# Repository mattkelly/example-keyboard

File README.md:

# example-keyboard

An example 4-key keyboard based on https://github.com/ruiqimao/keyboard-pcb-guide, with the following changes:

- Kailh Choc PG1350 switches
- Updated for KiCad 5
- 4-pin crystal in schematic to match footprint

## Firmware

Example QMK-based firmware is available on the [`example-keyboard` branch of my QMK fork](https://github.com/mattkelly/qmk_firmware/tree/example-keyboard/keyboards/example_keyboard).

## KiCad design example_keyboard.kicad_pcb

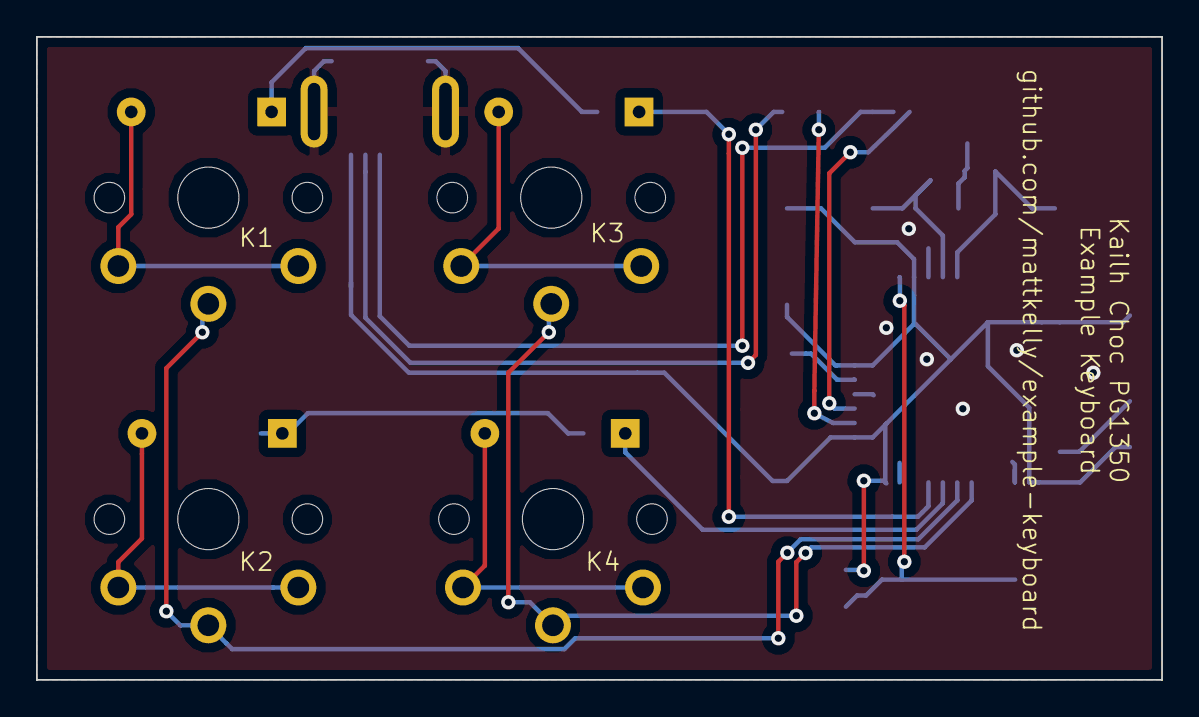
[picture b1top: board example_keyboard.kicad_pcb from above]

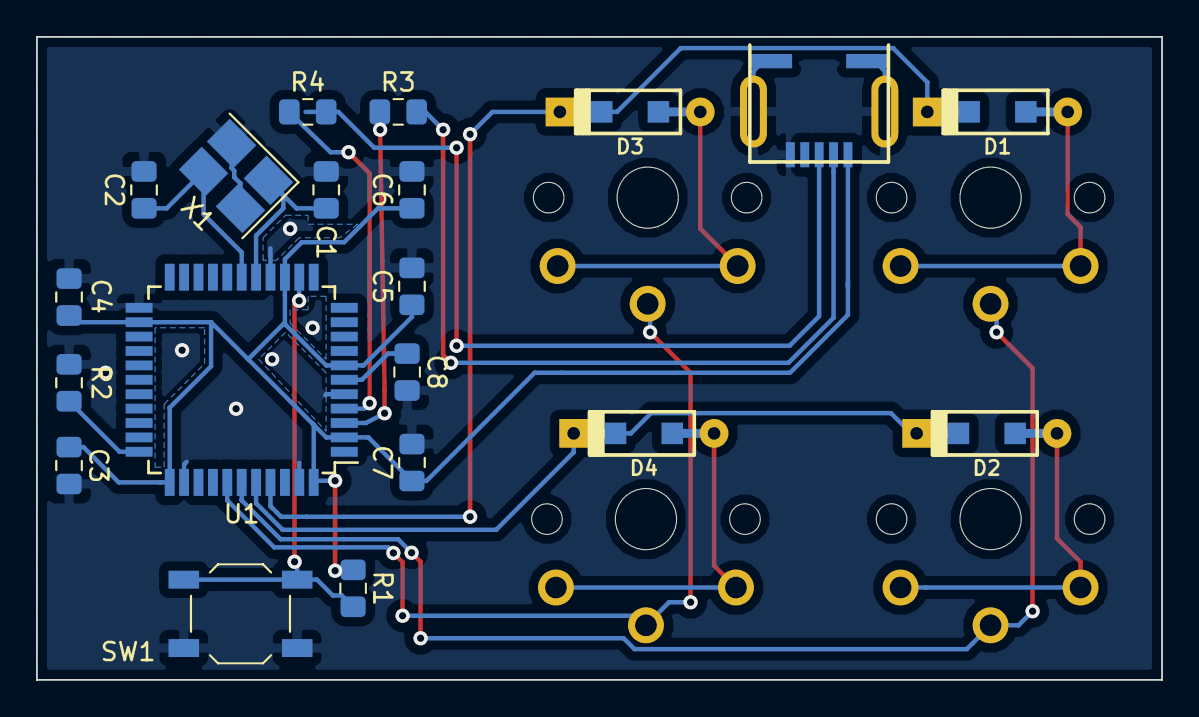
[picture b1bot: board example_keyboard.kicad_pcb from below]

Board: 2 copper layers, 62.5 x 35.7 mm, 24 parts (20 on the bottom side), 19 nets.

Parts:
C1, C2: 22p; C_0805_2012Metric_Pad1.15x1.40mm_HandSolder
C3, C4, C5, C6: 0.1u; C_0805_2012Metric_Pad1.15x1.40mm_HandSolder
C7: 4.7u; C_0805_2012Metric_Pad1.15x1.40mm_HandSolder
C8: 1u; C_0805_2012Metric_Pad1.15x1.40mm_HandSolder
D1, D2, D3, D4: D; D_SOD123_axial
J1: USB_mini_micro_B; USB_miniB_hirose_5S8
K1, K2, K3, K4: KEYSW; Kailh-PG1350-1u-reversible_NO_LED
R1, R2: 10k; R_0805_2012Metric_Pad1.15x1.40mm_HandSolder
R3, R4: 27; R_0805_2012Metric_Pad1.15x1.40mm_HandSolder
SW1: SW_PUSH; SW_SPST_TL3342
U1: ATMEGA32U4; TQFP-44_10x10mm_P0.8mm
X1: Crystal_GND24; Crystal_SMD_SeikoEpson_FA238-4Pin_3.2x2.5mm_HandSoldering

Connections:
/col0: K1.1, K2.1, U1.39
/col1: K3.1, K4.1, U1.38
/row0: D1.1, D3.1, U1.41
/row1: D2.1, D4.1, U1.40
GND: C1.2, C2.2, C3.2, C4.2, C5.2, C6.2, C7.2, C8.2, J1.5, J1.6, R2.2, SW1.1, U1.5, U1.15, U1.23, U1.35, U1.43, X1.2, X1.4
unnamed: C1.1, U1.16, X1.1
unnamed: C2.1, U1.17, X1.3
unnamed: C8.1, U1.6
unnamed: D1.2, K1.2
unnamed: D2.2, K2.2
unnamed: D3.2, K3.2
unnamed: D4.2, K4.2
unnamed: J1.2, R3.2
unnamed: J1.3, R4.2
unnamed: R1.2, SW1.2, U1.13
unnamed: R2.1, U1.33
unnamed: R3.1, U1.3
unnamed: R4.1, U1.4
VCC: C3.1, C4.1, C5.1, C6.1, C7.1, J1.1, R1.1, U1.2, U1.7, U1.14, U1.24, U1.34, U1.44

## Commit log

2019-03-08 Add the thing
2019-03-08 Fix off-board silkscreens, remove unneeded ground zones
2019-03-08 Add images
2019-03-08 Add more info, images
2019-03-19 Add link to firmware
